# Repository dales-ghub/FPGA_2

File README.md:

T20Q144 Development board. 
Has memory, power and multiple i/o

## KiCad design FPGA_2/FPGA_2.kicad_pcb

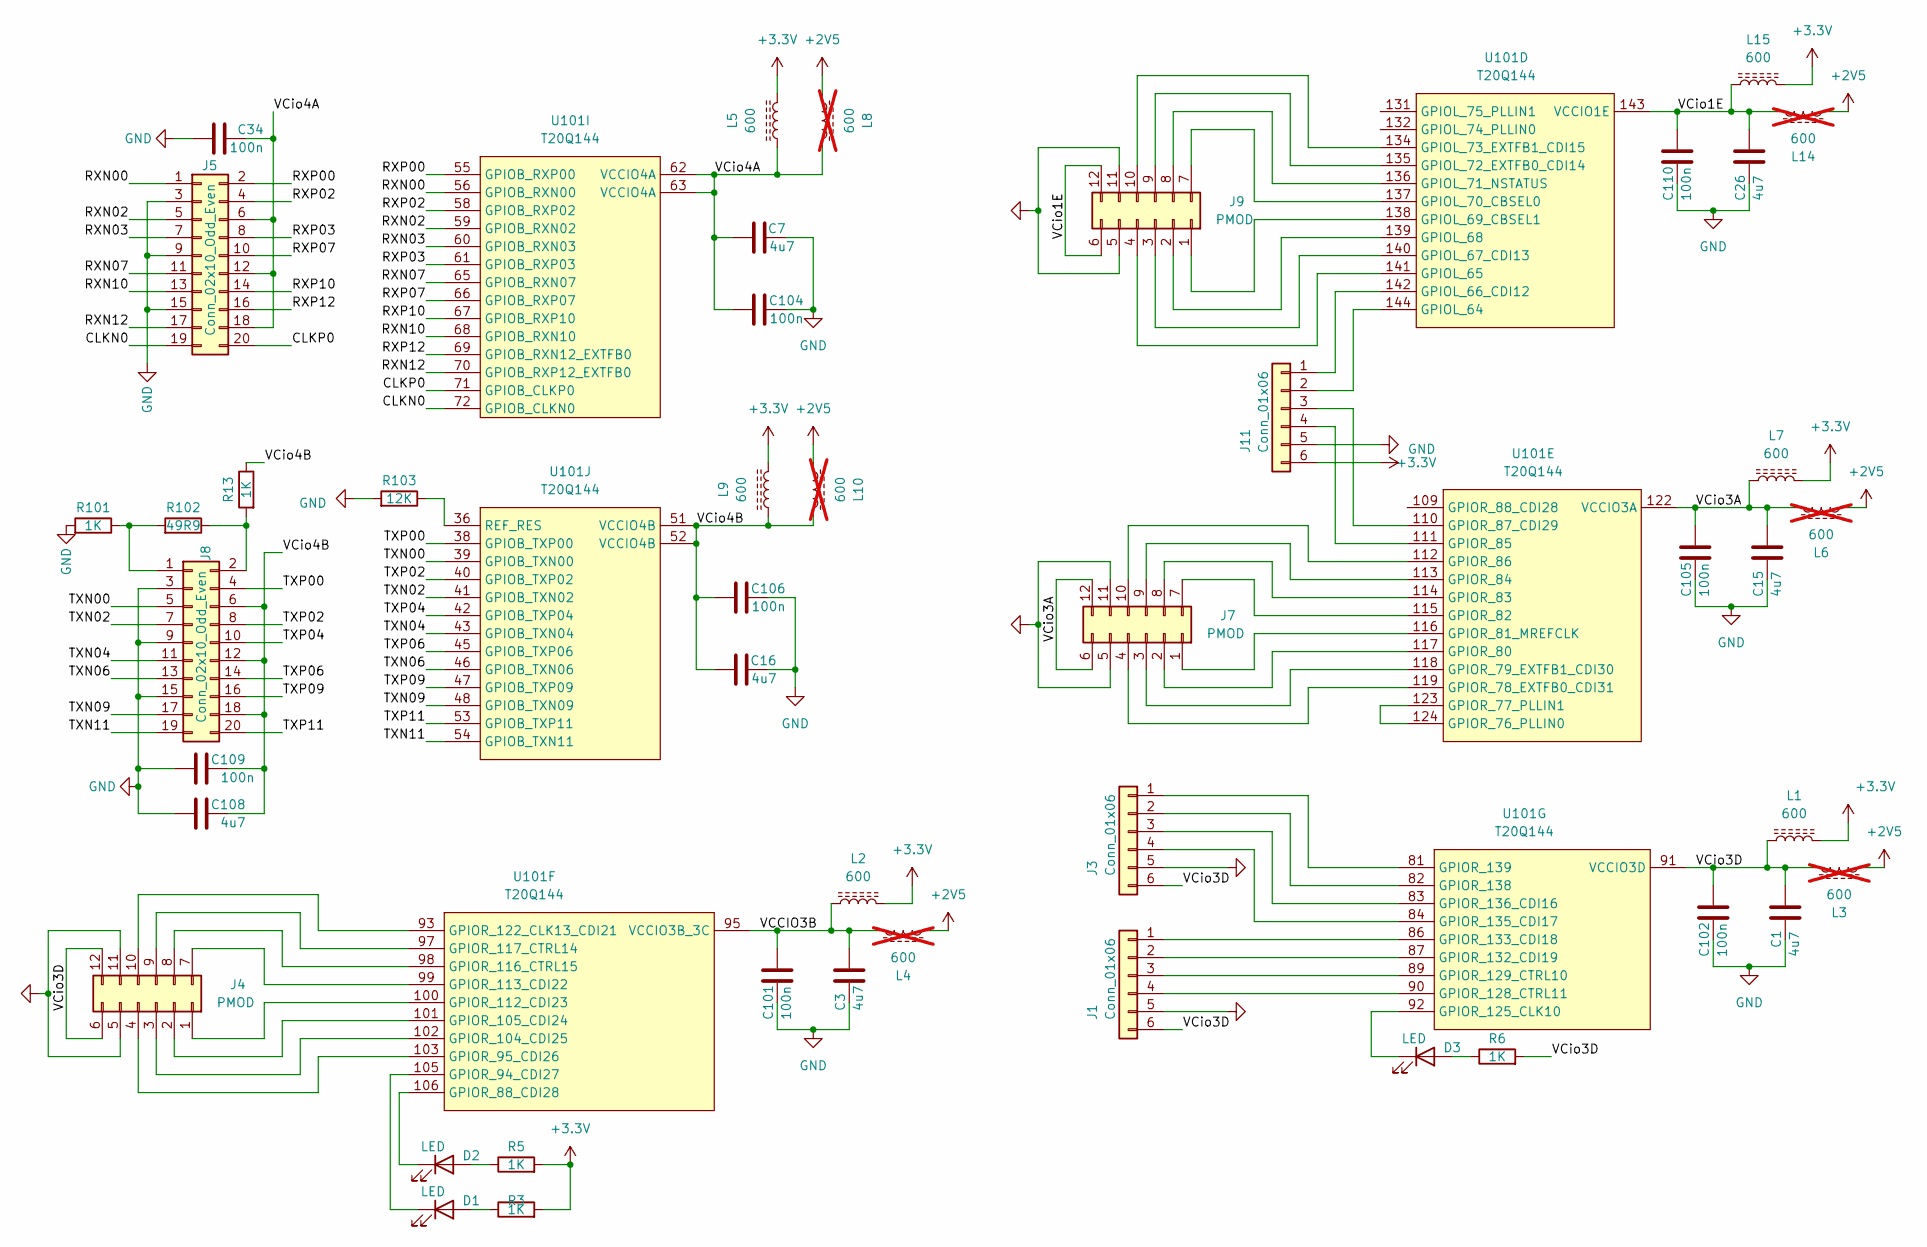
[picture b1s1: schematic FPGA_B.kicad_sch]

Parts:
C1, C3, C7, C15, C16, C26, C108: 4u7; C_0603_1608Metric
C34, C101, C102, C104, C105, C106, C109, C110: 100n; C_0402_1005Metric
D1, D2, D3: LED; LED_0603_1608Metric
J1, J3, J11: Conn_01x06; PinSocket_1x06_P2.54mm_Vertical
J4, J7, J9: PMOD; PMOD, Through hole
J5, J8: Conn_02x10_Odd_Even; PinSocket_2x10_P2.00mm_Vertical
L1, L2, L5, L7, L9, L15: 600; L_0603_1608Metric
L3, L4, L6, L8, L10, L14: 600; L_0603_1608Metric; not fitted
R3, R5, R6, R13, R101: 1K; R_0402_1005Metric
R102: 49R9; R_0402_1005Metric
R103: 12K; R_0402_1005Metric
U101: T20Q144; LQFP-144_20x20mm_P0.5mm

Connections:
+2V5: L3.1, L4.1, L6.1, L8.1, L10.1, L14.1; also elsewhere on the board
+3.3V: J11.6, L1.2, L2.2, L5.2, L7.2, L9.2, L15.2, R3.2, R5.2; also elsewhere on the board
/FPGA_B/CLKN0: J5.19, U101.72 (GPIOB_CLKN0)
/FPGA_B/CLKP0: J5.20, U101.71 (GPIOB_CLKP0)
/FPGA_B/RXN00: J5.1, U101.56 (GPIOB_RXN00)
/FPGA_B/RXN02: J5.5, U101.59 (GPIOB_RXN02)
/FPGA_B/RXN03: J5.7, U101.60 (GPIOB_RXN03)
/FPGA_B/RXN07: J5.11, U101.65 (GPIOB_RXN07)
/FPGA_B/RXN10: J5.13, U101.68 (GPIOB_RXN10)
/FPGA_B/RXN12: J5.17, U101.70 (GPIOB_RXP12_EXTFB0)
/FPGA_B/RXP00: J5.2, U101.55 (GPIOB_RXP00)
/FPGA_B/RXP02: J5.4, U101.58 (GPIOB_RXP02)
/FPGA_B/RXP03: J5.8, U101.61 (GPIOB_RXP03)
/FPGA_B/RXP07: J5.10, U101.66 (GPIOB_RXP07)
/FPGA_B/RXP10: J5.14, U101.67 (GPIOB_RXP10)
/FPGA_B/RXP12: J5.16, U101.69 (GPIOB_RXN12_EXTFB0)
/FPGA_B/TXN00: J8.5, U101.39 (GPIOB_TXN00)
/FPGA_B/TXN02: J8.7, U101.41 (GPIOB_TXN02)
/FPGA_B/TXN04: J8.11, U101.43 (GPIOB_TXN04)
/FPGA_B/TXN06: J8.13, U101.46 (GPIOB_TXN06)
/FPGA_B/TXN09: J8.17, U101.48 (GPIOB_TXN09)
/FPGA_B/TXN11: J8.19, U101.54 (GPIOB_TXN11)
/FPGA_B/TXP00: J8.4, U101.38 (GPIOB_TXP00)
/FPGA_B/TXP02: J8.8, U101.40 (GPIOB_TXP02)
/FPGA_B/TXP04: J8.10, U101.42 (GPIOB_TXP04)
/FPGA_B/TXP06: J8.14, U101.45 (GPIOB_TXP06)
/FPGA_B/TXP09: J8.16, U101.47 (GPIOB_TXP09)
/FPGA_B/TXP11: J8.20, U101.53 (GPIOB_TXP11)
/FPGA_B/VCCIO3B: C3.1, C101.1, L2.1, L4.2, U101.95 (VCCIO3B_3C)
/FPGA_B/VCio1E: C26.1, C110.1, J9.6, J9.12, L14.2, L15.1, U101.143 (VCCIO1E)
/FPGA_B/VCio3A: C15.1, C105.1, J7.6, J7.12, L6.2, L7.1, U101.122 (VCCIO3A)
/FPGA_B/VCio3D: C1.1, C102.1, J1.6, J3.6, J4.6, J4.12, L1.1, L3.2, R6.2, U101.91 (VCCIO3D)
/FPGA_B/VCio4A: C7.1, C34.2, C104.1, J5.6, J5.12, J5.18, L5.1, L8.2, U101.62 (VCCIO4A), U101.63 (VCCIO4A)
/FPGA_B/VCio4B: C16.1, C106.1, C108.2, C109.2, J8.6, J8.12, J8.18, L9.1, L10.2, R13.1, U101.51 (VCCIO4B), U101.52 (VCCIO4B)
GND: C1.2, C3.2, C7.2, C15.2, C16.2, C26.2, C34.1, C101.2, C102.2, C104.2, C105.2, C106.2, C108.1, C109.1, C110.2, J1.5, J3.5, J4.5, J4.11, J5.3, J5.9, J5.15, J7.5, J7.11, J8.3, J8.9, J8.15, J9.5, J9.11, J11.5, R101.2, R103.2; also elsewhere on the board
unnamed: D1.2 (A), R3.1
unnamed: D1.1 (K), U101.105 (GPIOR_94_CDI27)
unnamed: D2.2 (A), R5.1
unnamed: D2.1 (K), U101.106 (GPIOR_88_CDI28)
unnamed: D3.2 (A), R6.1
unnamed: D3.1 (K), U101.92 (GPIOR_125_CLK10)
unnamed: J1.1, U101.86 (GPIOR_133_CDI18)
unnamed: J1.2, U101.87 (GPIOR_132_CDI19)
unnamed: J1.3, U101.89 (GPIOR_129_CTRL10)
unnamed: J1.4, U101.90 (GPIOR_128_CTRL11)
unnamed: J3.1, U101.81 (GPIOR_139)
unnamed: J3.2, U101.82 (GPIOR_138)
unnamed: J3.3, U101.83 (GPIOR_136_CDI16)
unnamed: J3.4, U101.84 (GPIOR_135_CDI17)
unnamed: J4.1, U101.100 (GPIOR_112_CDI23)
unnamed: J4.2, U101.101 (GPIOR_105_CDI24)
unnamed: J4.3, U101.102 (GPIOR_104_CDI25)
unnamed: J4.4, U101.103 (GPIOR_95_CDI26)
unnamed: J4.7, U101.99 (GPIOR_113_CDI22)
unnamed: J4.8, U101.98 (GPIOR_116_CTRL15)
unnamed: J4.9, U101.97 (GPIOR_117_CTRL14)
unnamed: J4.10, U101.93 (GPIOR_122_CLK13_CDI21)
unnamed: J7.1, U101.116 (GPIOR_81_MREFCLK)
unnamed: J7.2, U101.117 (GPIOR_80)
unnamed: J7.3, U101.118 (GPIOR_79_EXTFB1_CDI30)
unnamed: J7.4, U101.119 (GPIOR_78_EXTFB0_CDI31)
unnamed: J7.7, U101.115 (GPIOR_82)
unnamed: J7.8, U101.114 (GPIOR_83)
unnamed: J7.9, U101.113 (GPIOR_84)
unnamed: J7.10, U101.112 (GPIOR_86)
unnamed: J8.1, R101.1, R102.2
unnamed: J8.2, R13.2, R102.1
unnamed: J9.1, U101.138 (GPIOL_69_CBSEL1)
unnamed: J9.2, U101.139 (GPIOL_68)
unnamed: J9.3, U101.140 (GPIOL_67_CDI13)
unnamed: J9.4, U101.141 (GPIOL_65)
unnamed: J9.7, U101.137 (GPIOL_70_CBSEL0)
unnamed: J9.8, U101.136 (GPIOL_71_NSTATUS)
unnamed: J9.9, U101.135 (GPIOL_72_EXTFB0_CDI14)
unnamed: J9.10, U101.134 (GPIOL_73_EXTFB1_CDI15)
unnamed: J11.1, U101.142 (GPIOL_66_CDI12)
unnamed: J11.2, U101.144 (GPIOL_64)
unnamed: J11.3, U101.110 (GPIOR_87_CDI29)
unnamed: J11.4, U101.111 (GPIOR_85)
unnamed: U101.123 (GPIOR_77_PLLIN1), U101.124 (GPIOR_76_PLLIN0)
unnamed: R103.1, U101.36 (REF_RES)

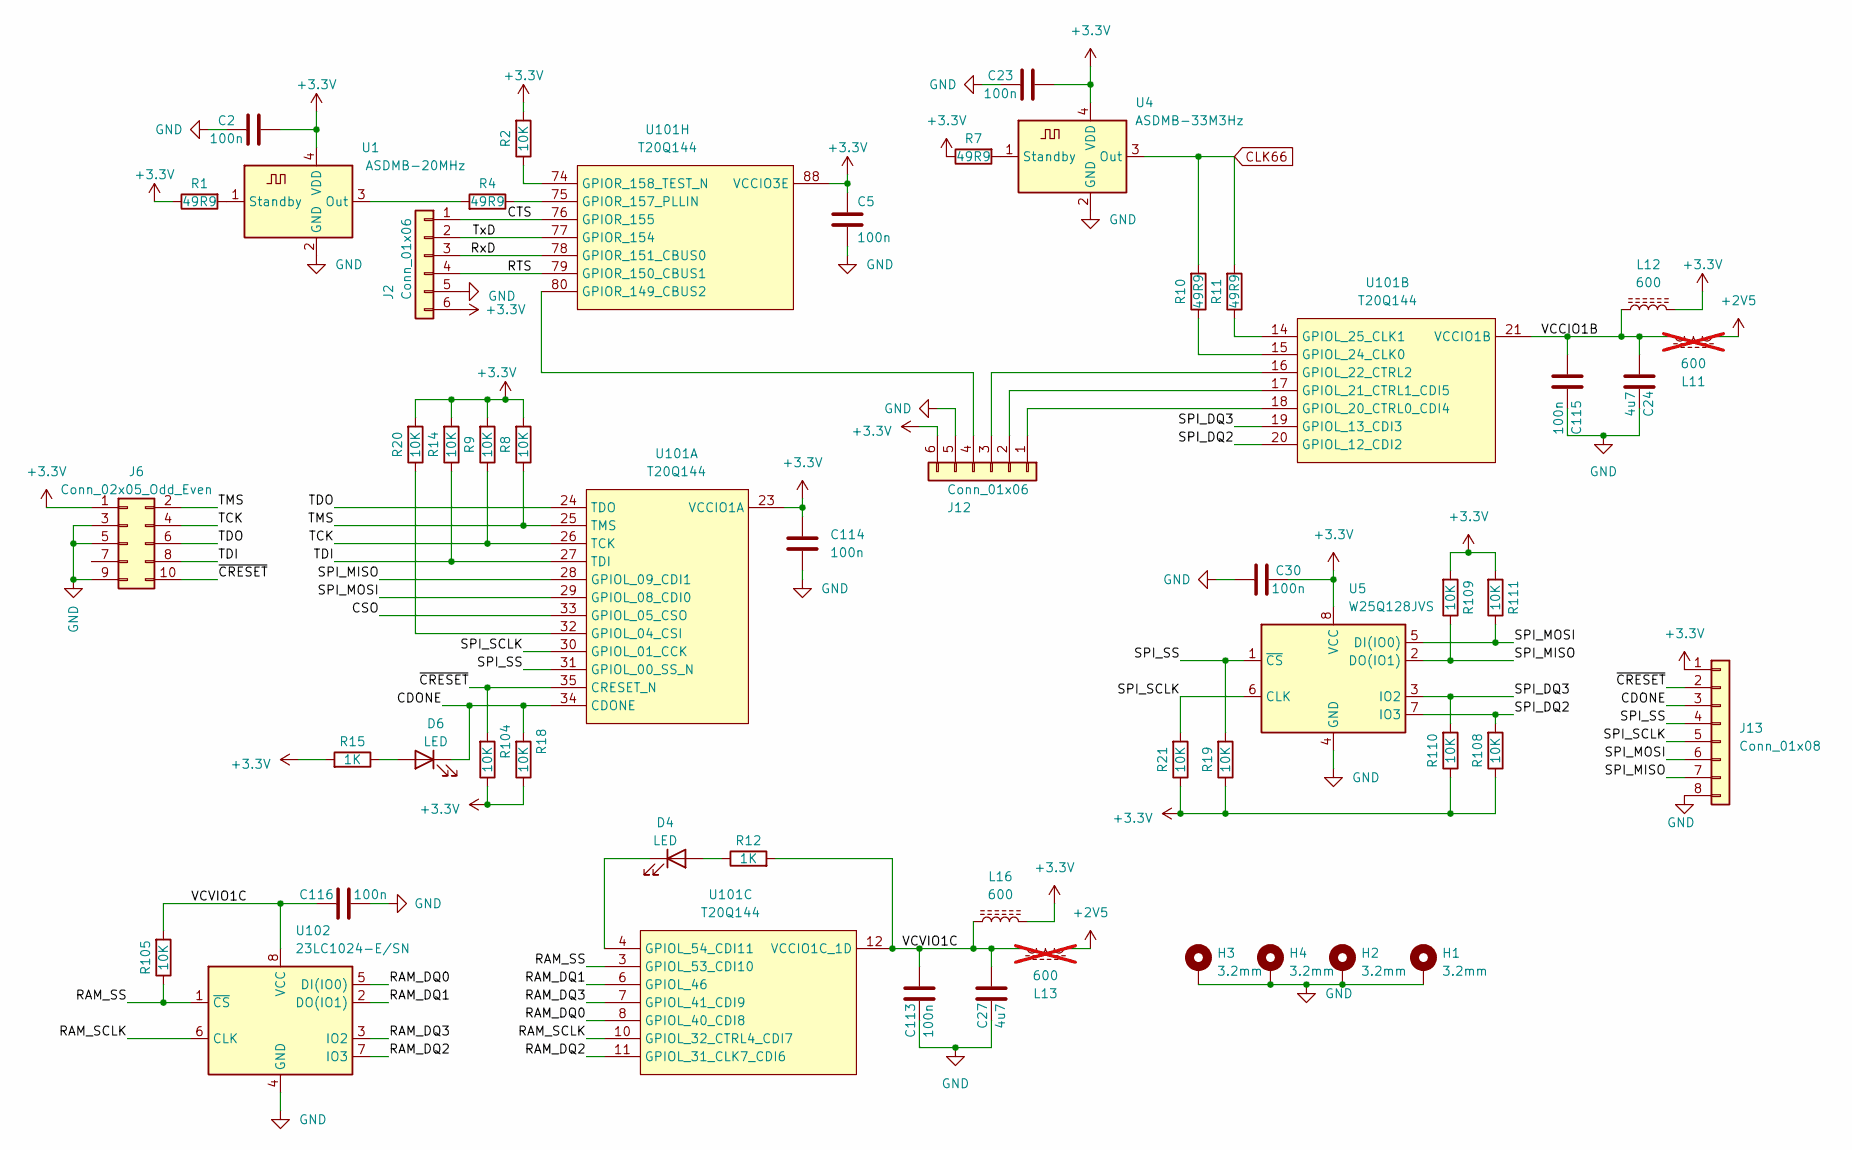
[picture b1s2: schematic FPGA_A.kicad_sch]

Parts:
C2, C5, C23, C30, C113, C114, C115, C116: 100n; C_0402_1005Metric
C24, C27: 4u7; C_0603_1608Metric
D4, D6: LED; LED_0603_1608Metric
H1, H2, H3, H4: 3.2mm; MountingHole_3.2mm_M3_Pad_TopBottom
J2, J12: Conn_01x06; PinSocket_1x06_P2.54mm_Vertical
J6: Conn_02x05_Odd_Even; PinHeader_2x05_P1.27mm_Vertical_SMD
J13: Conn_01x08; PinHeader_1x08_P2.54mm_Vertical
L11, L13: 600; L_0603_1608Metric; not fitted
L12, L16: 600; L_0603_1608Metric
R1, R4, R7, R10, R11: 49R9; R_0402_1005Metric
R2, R8, R9, R14, R18, R19, R20, R21, R104, R105, R108, R109, R110, R111: 10K; R_0402_1005Metric
R12, R15: 1K; R_0402_1005Metric
U1: ASDMB-20MHz; Oscillator_SMD_Abracon_ASDMB-4Pin_2.5x2.0mm
U4: ASDMB-33M3Hz; Oscillator_SMD_Abracon_ASDMB-4Pin_2.5x2.0mm
U5: W25Q128JVS; SOIC-8_5.23x5.23mm_P1.27mm
U101: T20Q144; LQFP-144_20x20mm_P0.5mm
U102: 23LC1024-E/SN; SOIC-8_5.23x5.23mm_P1.27mm

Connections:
+2V5: L11.1, L13.1; also elsewhere on the board
+3.3V: C2.1, C5.1, C23.1, C30.1, C114.1, J2.6, J6.1, J12.6, J13.1, L12.2, L16.2, R1.1, R2.2, R7.1, R8.2, R9.2, R14.2, R15.2, R18.1, R19.1, R20.2, R21.1, R104.1, R108.1, R109.2, R110.1, R111.2, U1.4 (VDD), U4.4 (VDD), U5.8 (VCC), U101.23 (VCCIO1A), U101.88 (VCCIO3E); also elsewhere on the board
/FPGA_A/CDONE: D6.1 (K), J13.3, R18.2, U101.34 (CDONE)
/FPGA_A/CSO: U101.33 (GPIOL_05_CSO)
/FPGA_A/CTS: J2.1, U101.76 (GPIOR_155)
/FPGA_A/RAM_DQ0: U101.8 (GPIOL_40_CDI8), U102.5 (DI(IO0))
/FPGA_A/RAM_DQ1: U101.6 (GPIOL_46), U102.2 (DO(IO1))
/FPGA_A/RAM_DQ2: U101.11 (GPIOL_31_CLK7_CDI6), U102.7 (IO3)
/FPGA_A/RAM_DQ3: U101.7 (GPIOL_41_CDI9), U102.3 (IO2)
/FPGA_A/RAM_SCLK: U101.10 (GPIOL_32_CTRL4_CDI7), U102.6 (CLK)
/FPGA_A/RAM_SS: R105.1, U101.3 (GPIOL_53_CDI10), U102.1 (~CS)
/FPGA_A/RTS: J2.4, U101.79 (GPIOR_150_CBUS1)
/FPGA_A/RxD: J2.3, U101.78 (GPIOR_151_CBUS0)
/FPGA_A/SPI_DQ2: R108.2, U5.7 (IO3), U101.20 (GPIOL_12_CDI2)
/FPGA_A/SPI_DQ3: R110.2, U5.3 (IO2), U101.19 (GPIOL_13_CDI3)
/FPGA_A/SPI_MISO: J13.7, R109.1, U5.2 (DO(IO1)), U101.28 (GPIOL_09_CDI1)
/FPGA_A/SPI_MOSI: J13.6, R111.1, U5.5 (DI(IO0)), U101.29 (GPIOL_08_CDI0)
/FPGA_A/SPI_SCLK: J13.5, R21.2, U5.6 (CLK), U101.30 (GPIOL_01_CCK)
/FPGA_A/SPI_SS: J13.4, R19.2, U5.1 (~CS), U101.31 (GPIOL_00_SS_N)
/FPGA_A/TCK: J6.4, R9.1, U101.26 (TCK)
/FPGA_A/TDI: J6.8, R14.1, U101.27 (TDI)
/FPGA_A/TDO: J6.6, U101.24 (TDO)
/FPGA_A/TMS: J6.2, R8.1, U101.25 (TMS)
/FPGA_A/TxD: J2.2, U101.77 (GPIOR_154)
/FPGA_A/VCCIO1B: C24.1, C115.1, L11.2, L12.1, U101.21 (VCCIO1B)
/FPGA_A/VCVIO1C: C27.1, C113.1, C116.2, L13.2, L16.1, R12.2, R105.2, U101.12 (VCCIO1C_1D), U102.8 (VCC)
/FPGA_A/~CRESET: J6.10, J13.2, R104.2, U101.35 (CRESET_N)
CLK66: R10.2, R11.2, U4.3 (Out)
GND: C2.2, C5.2, C23.2, C24.2, C27.2, C30.2, C113.2, C114.2, C115.2, C116.1, H1.1, H2.1, H3.1, H4.1, J2.5, J6.3, J6.5, J6.9, J12.5, J13.8, U1.2 (GND), U4.2 (GND), U5.4 (GND), U102.4 (GND); also elsewhere on the board
unnamed: D4.2 (A), R12.1
unnamed: D4.1 (K), U101.4 (GPIOL_54_CDI11)
unnamed: D6.2 (A), R15.1
unnamed: J12.1, U101.18 (GPIOL_20_CTRL0_CDI4)
unnamed: J12.2, U101.17 (GPIOL_21_CTRL1_CDI5)
unnamed: J12.3, U101.16 (GPIOL_22_CTRL2)
unnamed: J12.4, U101.80 (GPIOR_149_CBUS2)
unnamed: R4.2, U1.3 (Out)
unnamed: R1.2, U1.1 (Standby)
unnamed: R7.2, U4.1 (Standby)
unnamed: R20.1, U101.32 (GPIOL_04_CSI)
unnamed: R10.1, U101.15 (GPIOL_24_CLK0)
unnamed: R11.1, U101.14 (GPIOL_25_CLK1)
unnamed: R4.1, U101.75 (GPIOR_157_PLLIN)
unnamed: R2.1, U101.74 (GPIOR_158_TEST_N)

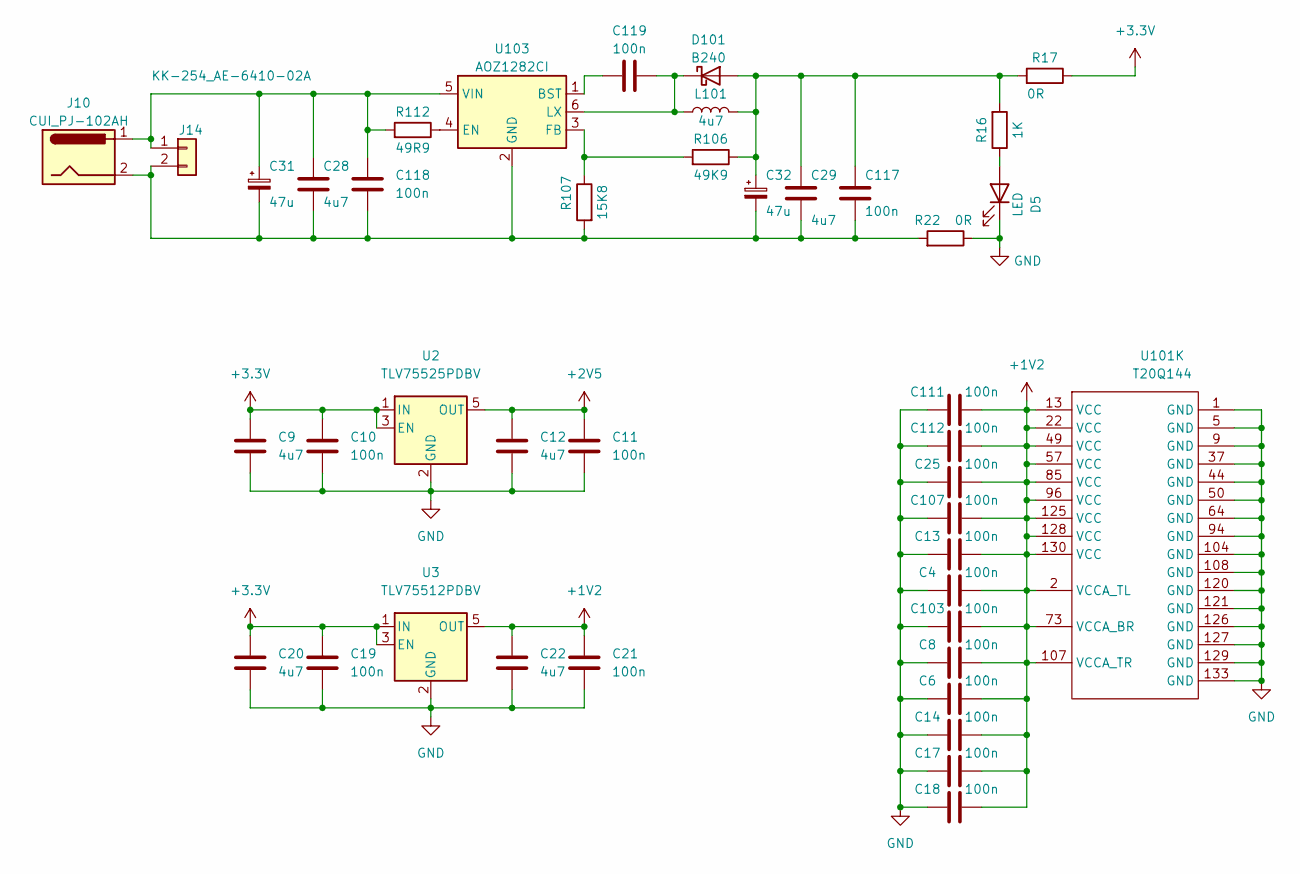
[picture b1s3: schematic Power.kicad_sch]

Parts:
C4, C6, C8, C10, C11, C13, C14, C17, C18, C19, C21, C25, C103, C107, C111, C112, C117, C118, C119: 100n; C_0402_1005Metric
C9, C12, C20, C22, C28, C29: 4u7; C_0603_1608Metric
C31, C32: 47u; CP_Elec_8x10
D5: LED; LED_0603_1608Metric
D101: B240; D_SMB
J10: CUI_PJ-102AH; BarrelJack_CUI_PJ-102AH_Horizontal
J14: KK-254_AE-6410-02A; Molex_KK-254_AE-6410-02A_1x02_P2.54mm_Vertical
L101: 4u7; L_Taiyo-Yuden_NR-50xx_HandSoldering
R16: 1K; R_0402_1005Metric
R17, R22: 0R; R_0402_1005Metric
R106: 49K9; R_0402_1005Metric
R107: 15K8; R_0402_1005Metric
R112: 49R9; R_0402_1005Metric
U2: TLV75525PDBV; SOT-23-5
U3: TLV75512PDBV; SOT-23-5
U101: T20Q144; LQFP-144_20x20mm_P0.5mm
U103: AOZ1282CI; SOT-23-6

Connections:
+1V2: C4.2, C6.2, C8.2, C13.2, C14.2, C17.2, C18.2, C21.1, C22.1, C25.2, C103.2, C107.2, C111.2, C112.2, U3.5 (OUT), U101.2 (VCCA_TL), U101.13 (VCC), U101.22 (VCC), U101.49 (VCC), U101.57 (VCC), U101.73 (VCCA_BR), U101.85 (VCC), U101.96 (VCC), U101.107 (VCCA_TR), U101.125 (VCC), U101.128 (VCC), U101.130 (VCC)
+2V5: C11.1, C12.1, U2.5 (OUT); also elsewhere on the board
+3.3V: C9.1, C10.1, C19.1, C20.1, R17.1, U2.1 (IN), U2.3 (EN), U3.1 (IN), U3.3 (EN); also elsewhere on the board
GND: C4.1, C6.1, C8.1, C9.2, C10.2, C11.2, C12.2, C13.1, C14.1, C17.1, C18.1, C19.2, C20.2, C21.2, C22.2, C25.1, C103.1, C107.1, C111.1, C112.1, D5.1 (K), R22.1, U2.2 (GND), U3.2 (GND), U101.1 (GND), U101.5 (GND), U101.9 (GND), U101.37 (GND), U101.44 (GND), U101.50 (GND), U101.64 (GND), U101.94 (GND), U101.104 (GND), U101.108 (GND), U101.120 (GND), U101.121 (GND), U101.126 (GND), U101.127 (GND), U101.129 (GND), U101.133 (GND); also elsewhere on the board
unnamed: D5.2 (A), R16.1
unnamed: C29.1, C32.1, C117.1, D101.2 (A), L101.2, R16.2, R17.2, R106.1
unnamed: C119.1, D101.1 (K), L101.1, U103.6 (LX)
unnamed: C28.1, C31.1, C118.1, J10.1, J14.1, R112.2, U103.5 (VIN)
unnamed: C28.2, C29.2, C31.2, C32.2, C117.2, C118.2, J10.2, J14.2, R22.2, R107.2, U103.2 (GND)
unnamed: C119.2, U103.1 (BST)
unnamed: R112.1, U103.4 (EN)
unnamed: R106.2, R107.1, U103.3 (FB)

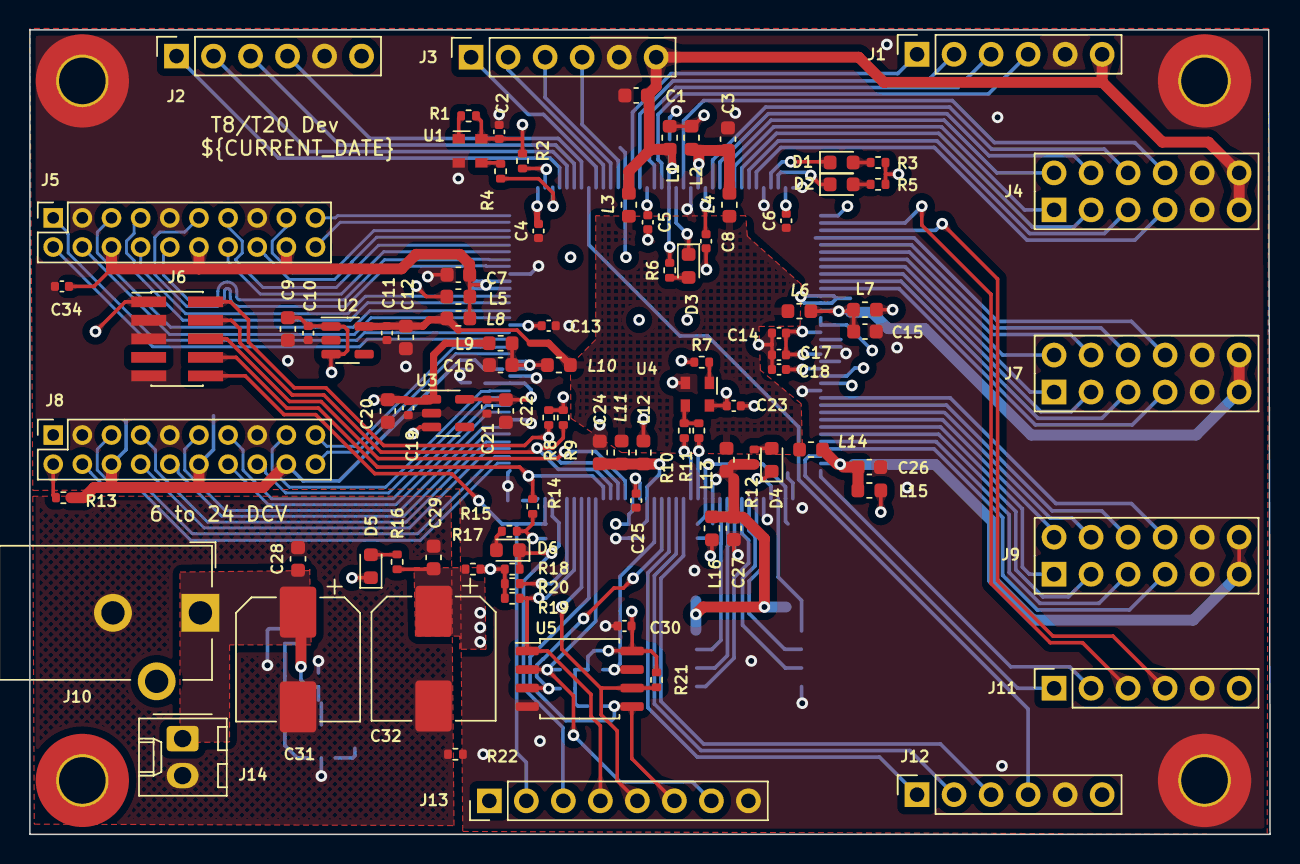
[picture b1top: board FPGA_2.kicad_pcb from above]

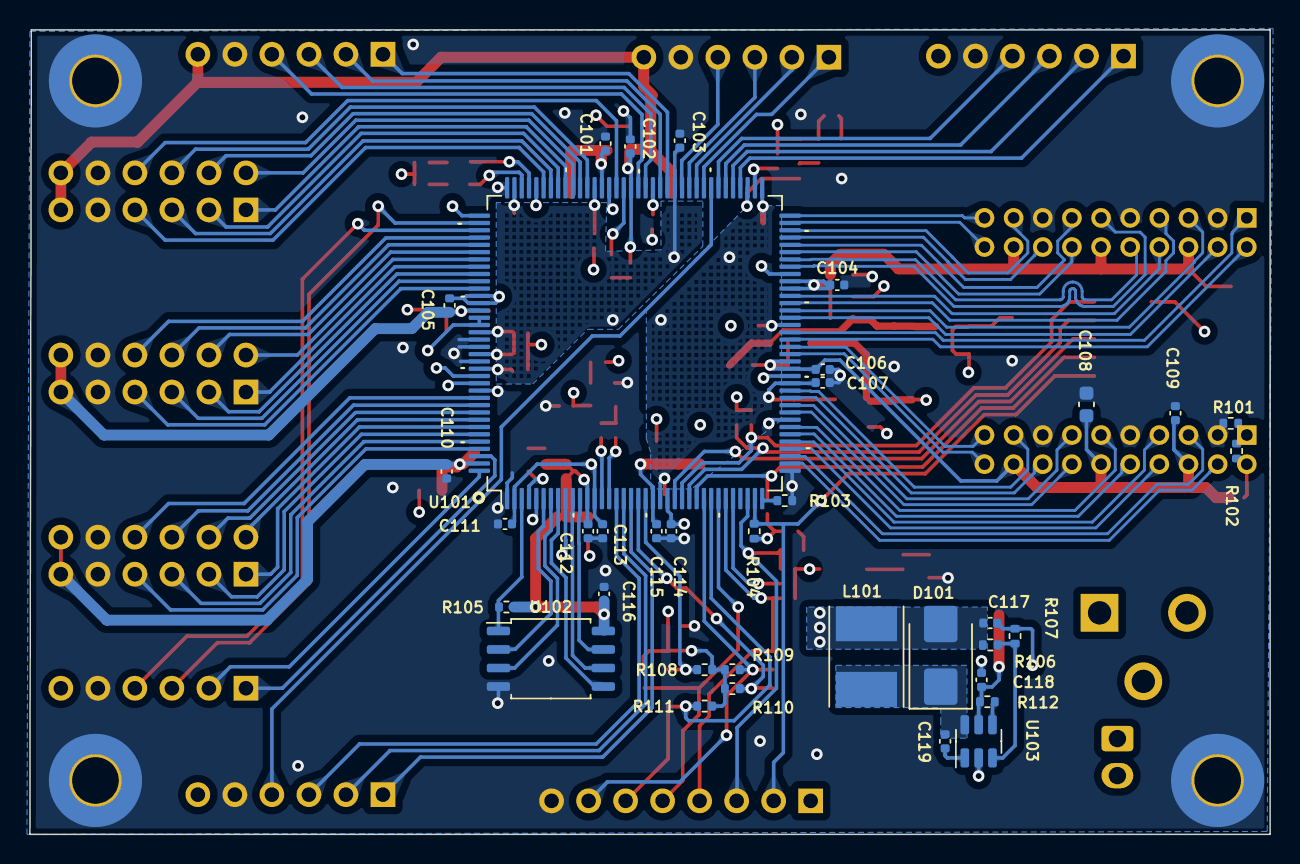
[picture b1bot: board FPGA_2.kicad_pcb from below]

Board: 4 copper layers, 85.1 x 55.2 mm, 136 parts (36 on the bottom side), 130 nets.

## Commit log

2025-03-07 Efinix 144 pin qfp development board.
